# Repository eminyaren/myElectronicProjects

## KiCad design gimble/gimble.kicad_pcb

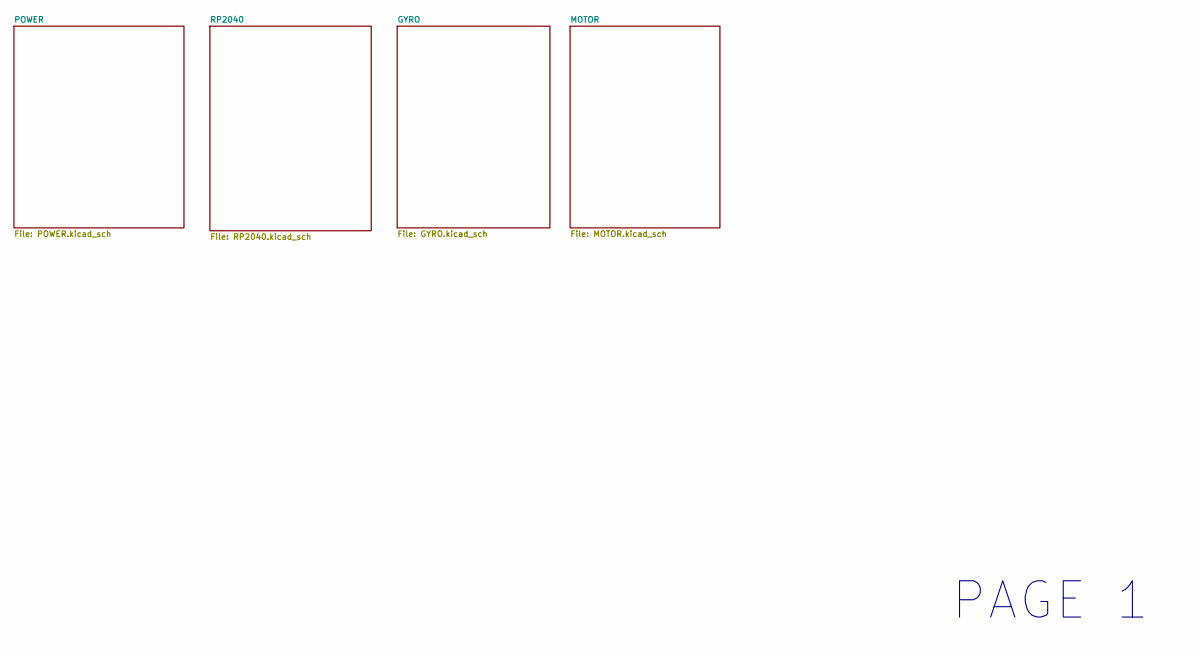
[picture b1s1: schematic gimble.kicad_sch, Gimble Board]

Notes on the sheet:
PAGE 1

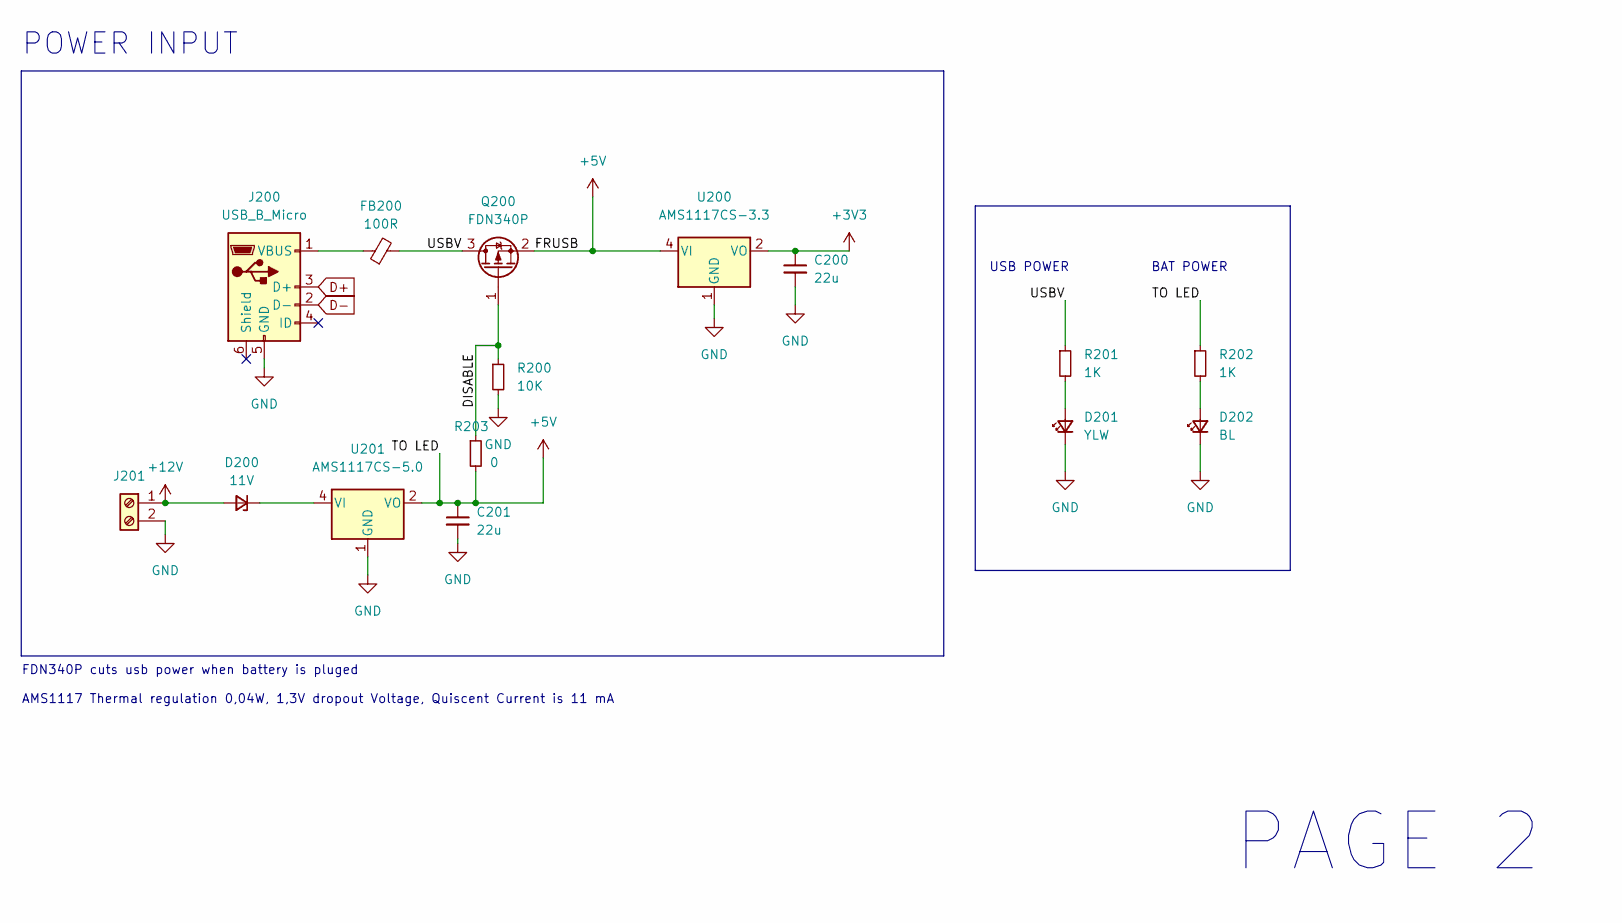
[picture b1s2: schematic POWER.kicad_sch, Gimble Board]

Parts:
C200, C201: 22u; CP_EIA-1608-08_AVX-J
D200: 11V; D_0603_1608Metric
D201: YLW; LED_0402_1005Metric
D202: BL; LED_0402_1005Metric
FB200: 100R; D_0603_1608Metric
J200: USB_B_Micro; USB_Micro-B_Molex_47346-0001
J201: Screw_Terminal_01x02; Molex_KK-254_AE-6410-02A_1x02_P2.54mm_Vertical
Q200: FDN340P; SOT-23
R200: 10K; R_0402_1005Metric
R201, R202: 1K; R_0402_1005Metric
R203: 0; R_0402_1005Metric
U200: AMS1117CS-3.3; SOIC-8_3.9x4.9mm_P1.27mm
U201: AMS1117CS-5.0; SOIC-8_3.9x4.9mm_P1.27mm

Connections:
+3V3: C200.1, U200.2 (VO), U200.3 (VO), U200.6 (VO), U200.7 (VO); also elsewhere on the board
+5V: C201.1, Q200.2 (S), R202.1, R203.2, U200.4 (VI), U201.2 (VO), U201.3 (VO), U201.6 (VO), U201.7 (VO); also elsewhere on the board
+12V: D200.2 (A), J201.1
/POWER/DISABLE: Q200.1 (G), R200.1, R203.1
/POWER/USBV: FB200.2, Q200.3 (D), R201.1
D+: J200.3 (D+); also elsewhere on the board
D-: J200.2 (D-); also elsewhere on the board
GND: C200.2, C201.2, D201.1 (K), D202.1 (K), J200.5 (GND), J201.2, R200.2, U200.1 (GND), U201.1 (GND); also elsewhere on the board
unnamed: D200.1 (K), U201.4 (VI)
unnamed: FB200.1, J200.1 (VBUS)
unnamed: D201.2 (A), R201.2
unnamed: D202.2 (A), R202.2

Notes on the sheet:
BAT POWER
PAGE 2
FDN340P cuts usb power when battery is pluged AMS1117 Thermal regulation 0,04W, 1,3V dropout Voltage, Quiscent Current is 11 mA
USB POWER
POWER INPUT

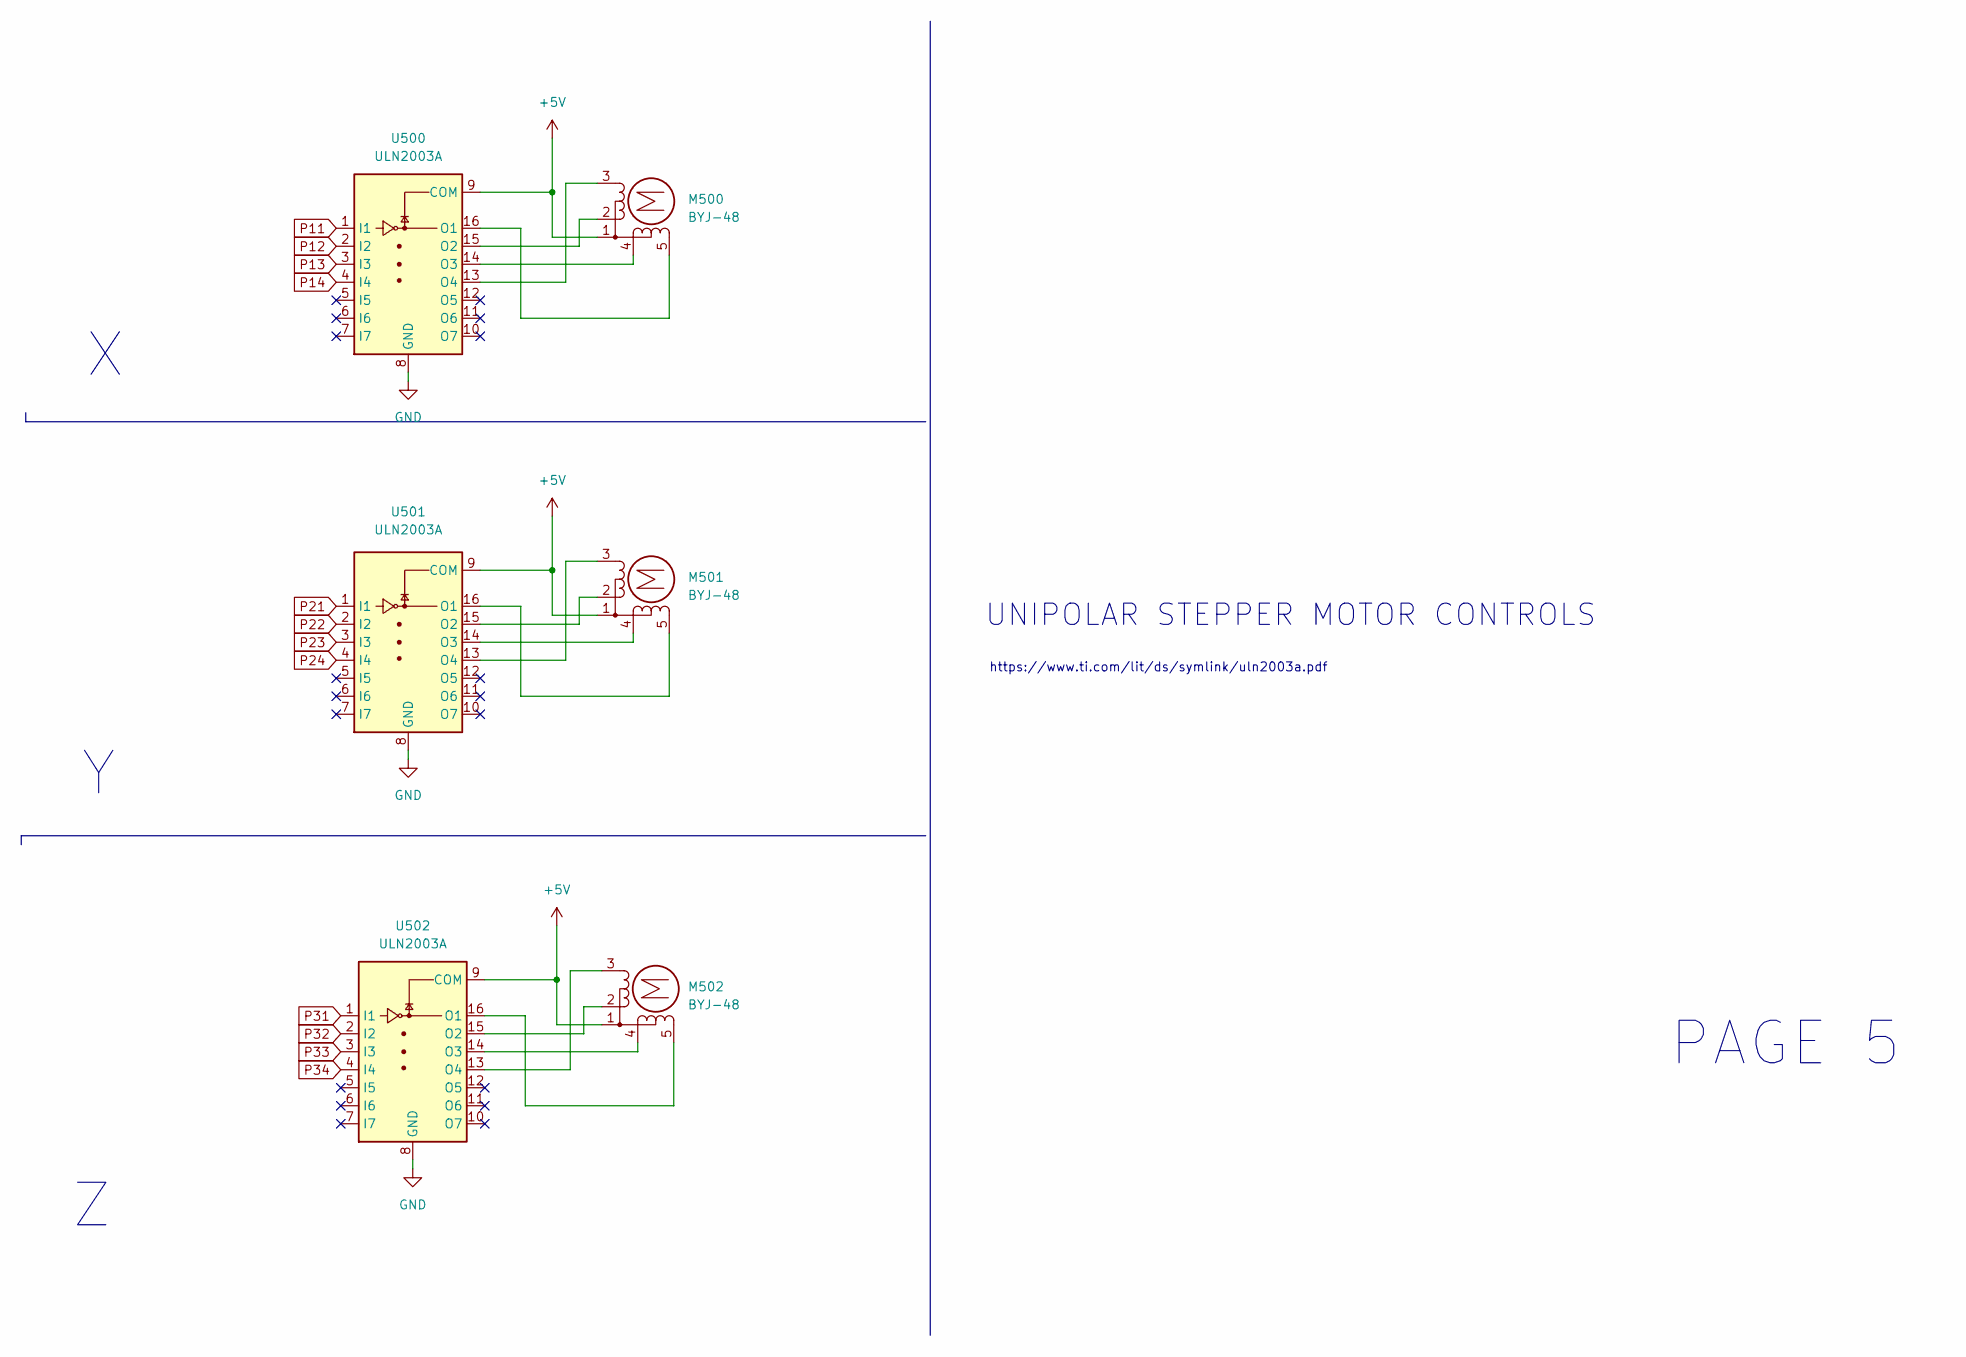
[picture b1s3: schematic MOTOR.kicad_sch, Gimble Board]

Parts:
M500, M501, M502: BYJ-48; PinHeader_1x05_P1.00mm_Vertical
U500, U501, U502: ULN2003A; SOIC-16_3.9x9.9mm_P1.27mm

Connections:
+5V: M500.1, M501.1, M502.1, U500.9 (COM), U501.9 (COM), U502.9 (COM); also elsewhere on the board
GND: U500.8 (GND), U501.8 (GND), U502.8 (GND); also elsewhere on the board
unnamed: M500.2, U500.15 (O2)
unnamed: M500.3 (-), U500.13 (O4)
unnamed: M500.4, U500.14 (O3)
unnamed: M500.5, U500.16 (O1)
unnamed: M501.3 (-), U501.13 (O4)
unnamed: M501.4, U501.14 (O3)
unnamed: M501.2, U501.15 (O2)
unnamed: M501.5, U501.16 (O1)
unnamed: M502.3 (-), U502.13 (O4)
unnamed: M502.4, U502.14 (O3)
unnamed: M502.2, U502.15 (O2)
unnamed: M502.5, U502.16 (O1)
P11: U500.1 (I1); also elsewhere on the board
P12: U500.2 (I2); also elsewhere on the board
P13: U500.3 (I3); also elsewhere on the board
P14: U500.4 (I4); also elsewhere on the board
P21: U501.1 (I1); also elsewhere on the board
P22: U501.2 (I2); also elsewhere on the board
P23: U501.3 (I3); also elsewhere on the board
P24: U501.4 (I4); also elsewhere on the board
P31: U502.1 (I1); also elsewhere on the board
P32: U502.2 (I2); also elsewhere on the board
P33: U502.3 (I3); also elsewhere on the board
P34: U502.4 (I4); also elsewhere on the board

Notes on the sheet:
UNIPOLAR STEPPER MOTOR CONTROLS
https://www.ti.com/lit/ds/symlink/uln2003a.pdf
PAGE 5

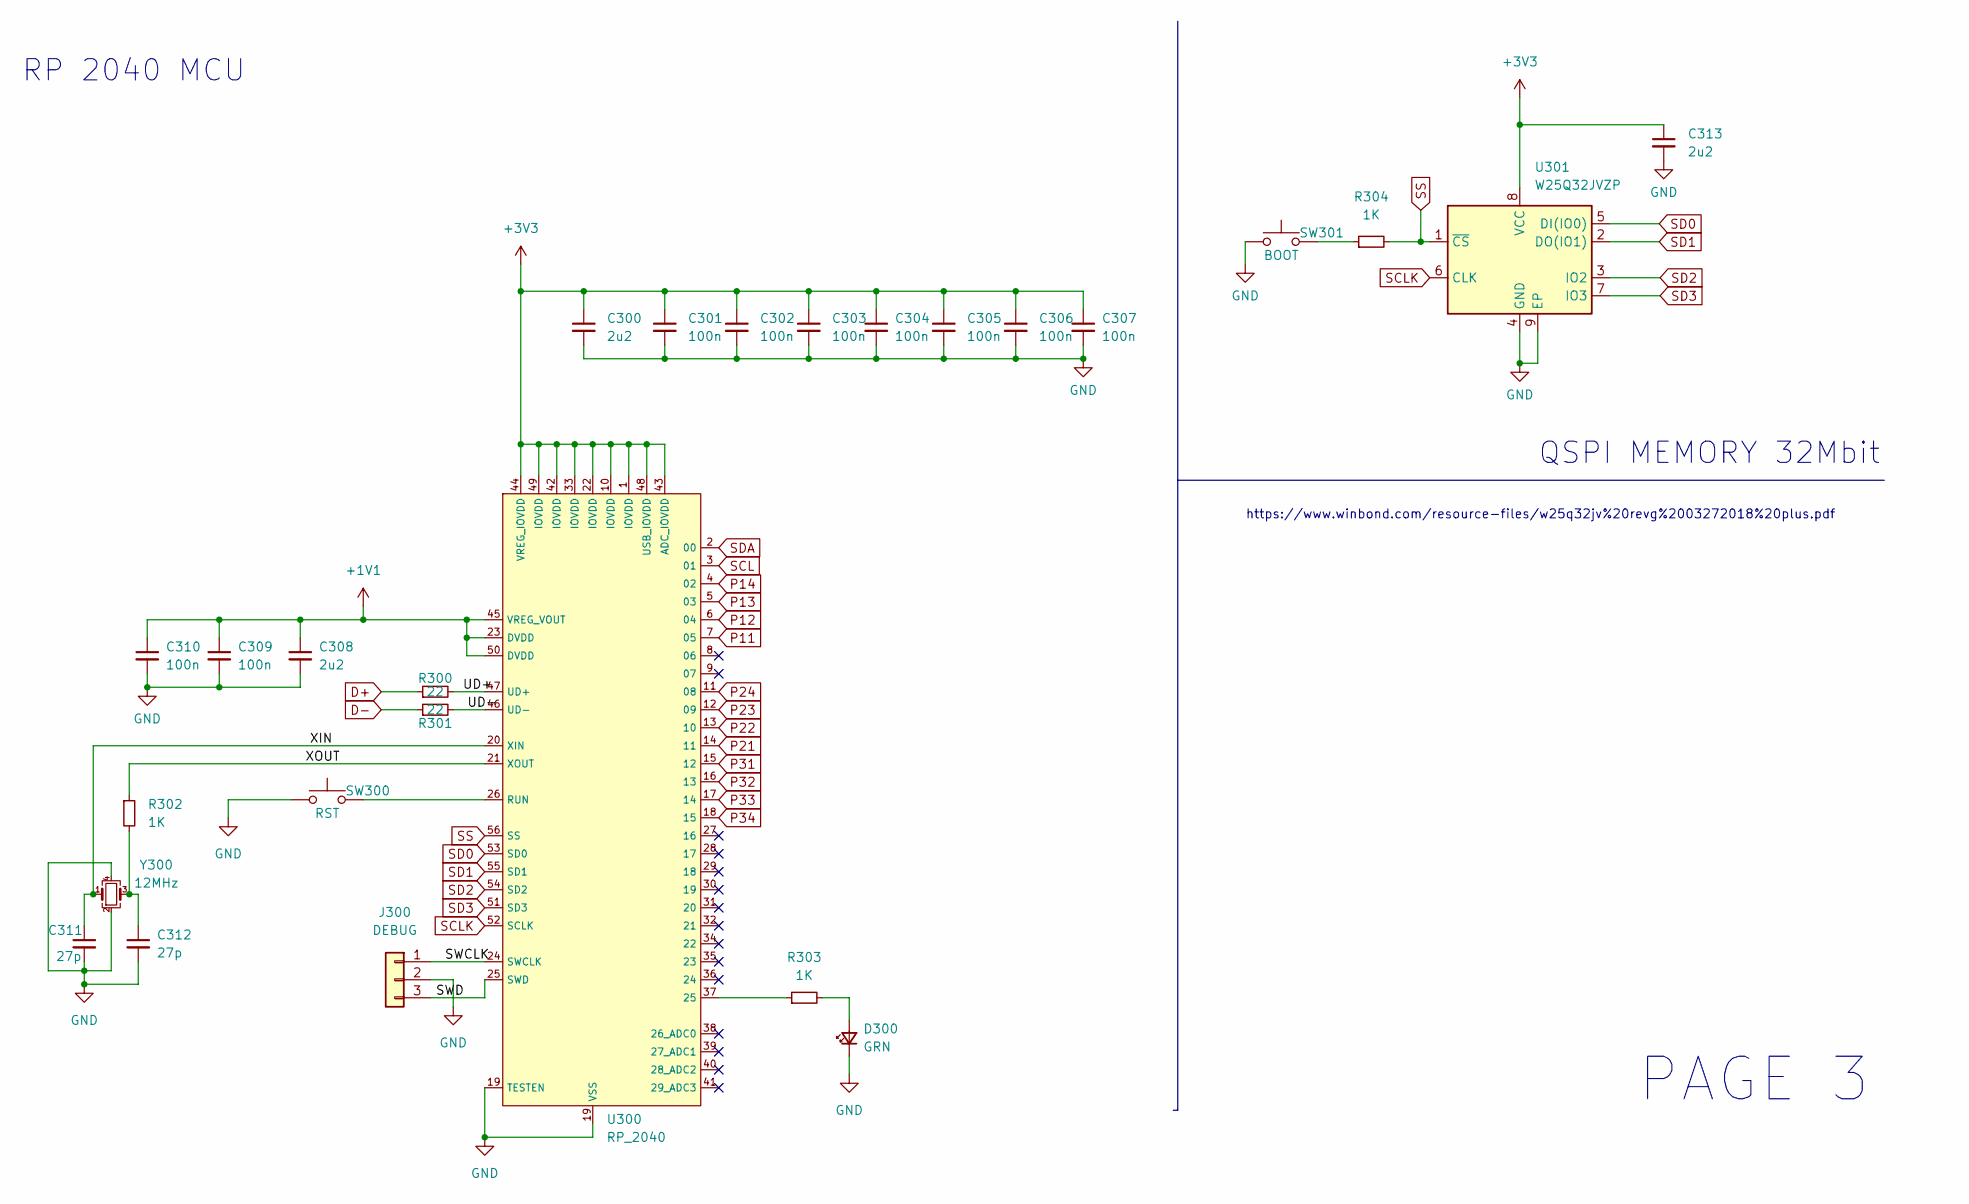
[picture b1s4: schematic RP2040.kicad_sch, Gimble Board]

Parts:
C300, C308, C313: 2u2; C_0603_1608Metric
C301, C302, C303, C304, C305, C306, C307, C309, C310: 100n; C_0402_1005Metric
C311, C312: 27p; C_0402_1005Metric
D300: GRN; LED_0402_1005Metric
J300: DEBUG; PinHeader_1x03_P2.54mm_Vertical
R300, R301: 22; R_0402_1005Metric
R302, R303, R304: 1K; R_0402_1005Metric
SW300: RST; SW_SPST_B3U-3000P
SW301: BOOT; SW_SPST_B3U-3000P
U300: RP_2040
U301: W25Q32JVZP; WSON-8-1EP_6x5mm_P1.27mm_EP3.4x4.3mm
Y300: 12MHz; Crystal_SMD_3225-4Pin_3.2x2.5mm

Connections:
+1V1: C308.1, C309.1, C310.1, U300.23 (DVDD), U300.45 (VREG_VOUT), U300.50 (DVDD)
+3V3: C300.1, C301.1, C302.1, C303.1, C304.1, C305.1, C306.1, C307.1, C313.1, U300.1 (IOVDD), U300.10 (IOVDD), U300.22 (IOVDD), U300.33 (IOVDD), U300.42 (IOVDD), U300.43 (ADC_IOVDD), U300.44 (VREG_IOVDD), U300.48 (USB_IOVDD), U300.49 (IOVDD), U301.8 (VCC); also elsewhere on the board
/RP2040/SWCLK: J300.1, U300.24 (SWCLK)
/RP2040/SWD: J300.3, U300.25 (SWD)
/RP2040/UD+: R300.2, U300.47 (UD+)
/RP2040/UD-: R301.2, U300.46 (UD-)
/RP2040/XIN: C311.1, U300.20 (XIN), Y300.1
/RP2040/XOUT: R302.1, U300.21 (XOUT)
D+: R300.1; also elsewhere on the board
D-: R301.1; also elsewhere on the board
GND: C300.2, C301.2, C302.2, C303.2, C304.2, C305.2, C306.2, C307.2, C308.2, C309.2, C310.2, C311.2, C312.2, C313.2, D300.1 (K), J300.2, SW300.1, SW301.1, U300.19 (TESTEN), U300.57, U301.4 (GND), U301.9 (EP), Y300.2, Y300.4; also elsewhere on the board
unnamed: C312.1, R302.2, Y300.3
unnamed: D300.2 (A), R303.2
unnamed: R304.1, SW301.2
unnamed: SW300.2, U300.26 (RUN)
unnamed: R303.1, U300.37 (25)
P11: U300.7 (05); also elsewhere on the board
P12: U300.6 (04); also elsewhere on the board
P13: U300.5 (03); also elsewhere on the board
P14: U300.4 (02); also elsewhere on the board
P21: U300.14 (11); also elsewhere on the board
P22: U300.13 (10); also elsewhere on the board
P23: U300.12 (09); also elsewhere on the board
P24: U300.11 (08); also elsewhere on the board
P31: U300.15 (12); also elsewhere on the board
P32: U300.16 (13); also elsewhere on the board
P33: U300.17 (14); also elsewhere on the board
P34: U300.18 (15); also elsewhere on the board
SCL: U300.3 (01); also elsewhere on the board
SCLK: U300.52 (SCLK), U301.6 (CLK)
SD0: U300.53 (SD0), U301.5 (DI(IO0))
SD1: U300.55 (SD1), U301.2 (DO(IO1))
SD2: U300.54 (SD2), U301.3 (IO2)
SD3: U300.51 (SD3), U301.7 (IO3)
SDA: U300.2 (00); also elsewhere on the board
SS: R304.2, U300.56 (SS), U301.1 (~CS)

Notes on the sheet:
QSPI MEMORY 32Mbit
PAGE 3
RP 2040 MCU
https://www.winbond.com/resource-files/w25q32jv%20revg%2003272018%20plus.pdf

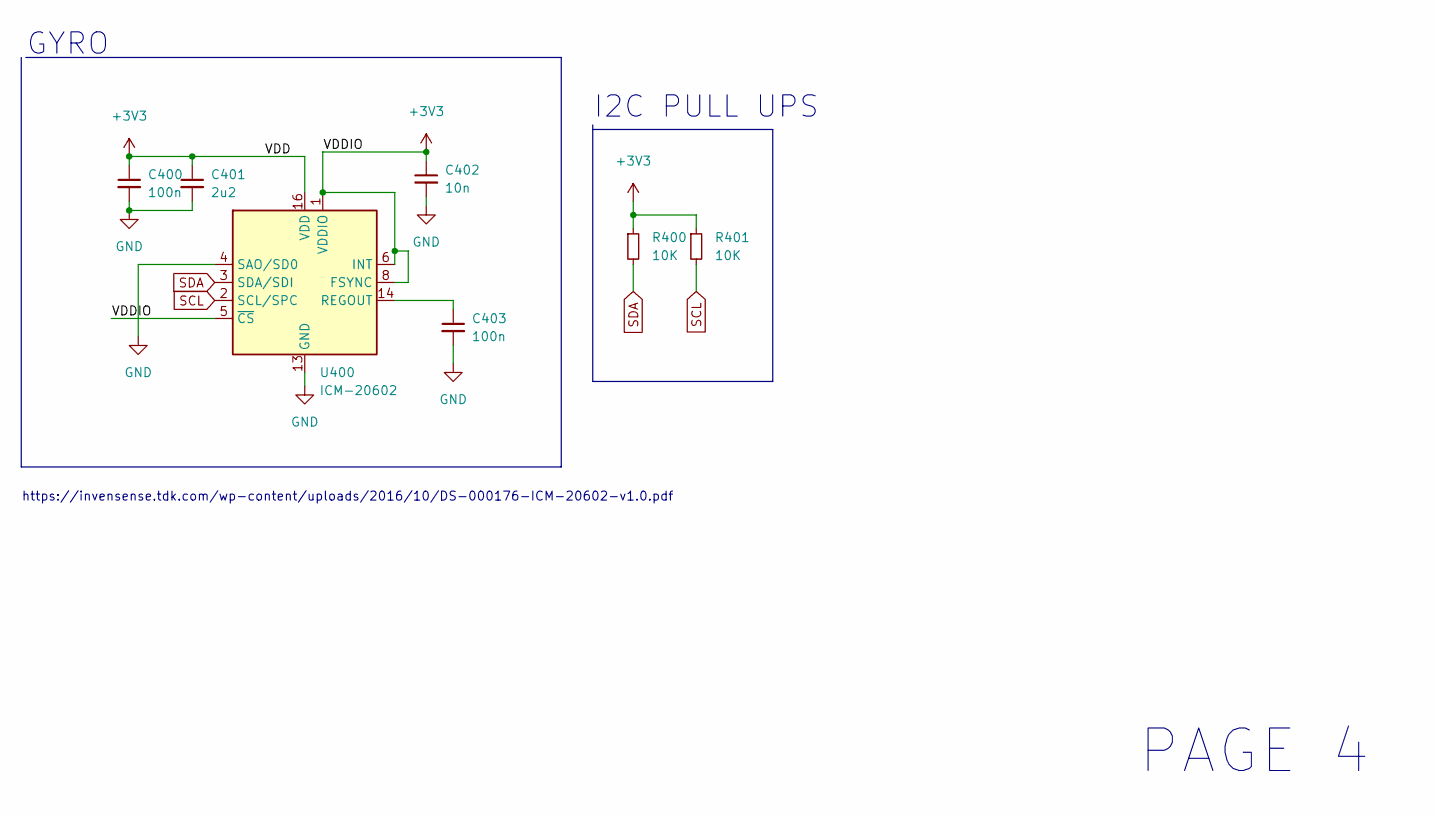
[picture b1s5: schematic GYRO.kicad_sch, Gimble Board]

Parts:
C400, C403: 100n; C_0402_1005Metric
C401: 2u2; C_0603_1608Metric
C402: 10n; C_0402_1005Metric
R400, R401: 10K; R_0402_1005Metric
U400: ICM-20602; LGA-16_3x3mm_P0.5mm_LayoutBorder3x5y

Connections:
+3V3: C400.1, C401.1, C402.1, R400.1, R401.1, U400.1 (VDDIO), U400.5 (~CS), U400.6 (INT), U400.8 (FSYNC), U400.16 (VDD); also elsewhere on the board
GND: C400.2, C401.2, C402.2, C403.2, U400.4 (SAO/SD0), U400.9 (GND), U400.10 (GND), U400.11 (GND), U400.12 (GND), U400.13 (GND), U400.15 (GND); also elsewhere on the board
unnamed: C403.1, U400.14 (REGOUT)
SCL: R401.2, U400.2 (SCL/SPC); also elsewhere on the board
SDA: R400.2, U400.3 (SDA/SDI); also elsewhere on the board

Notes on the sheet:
I2C PULL UPS
https://invensense.tdk.com/wp-content/uploads/2016/10/DS-000176-ICM-20602-v1.0.pdf
PAGE 4
GYRO

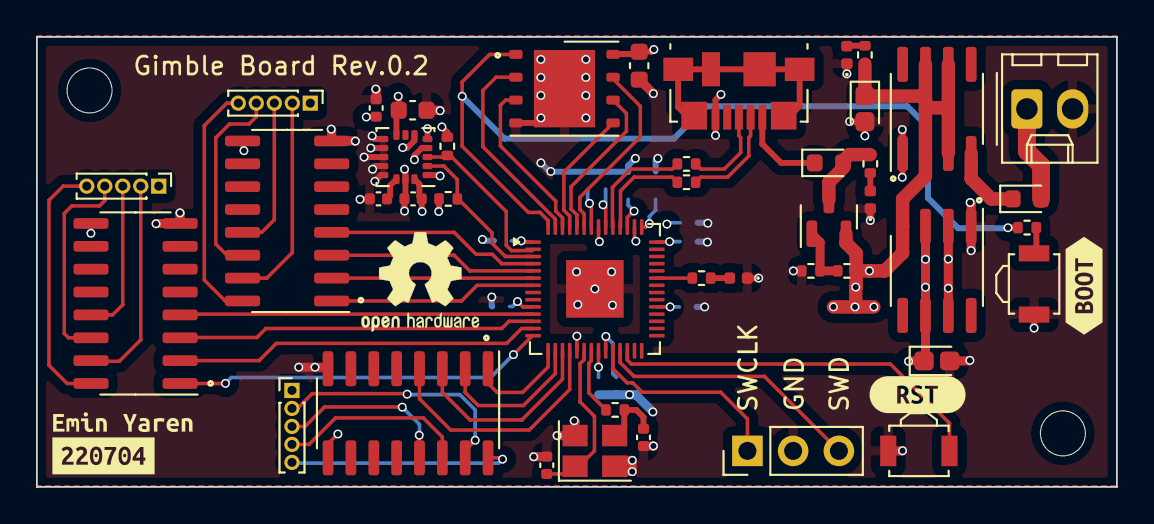
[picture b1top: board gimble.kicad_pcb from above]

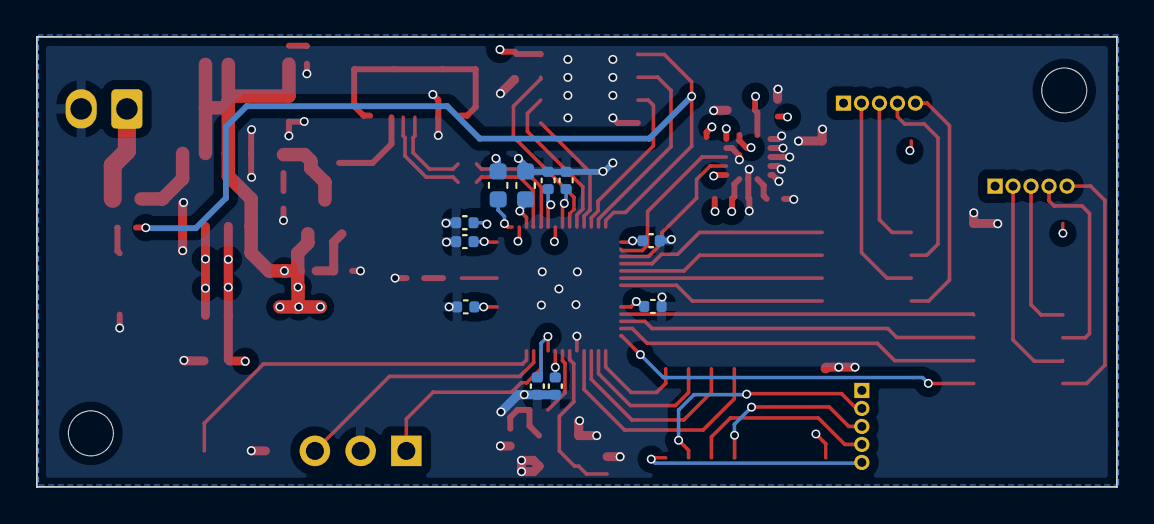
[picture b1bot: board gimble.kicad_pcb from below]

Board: 4 copper layers, 60.0 x 25.0 mm, 58 parts (11 on the bottom side), 57 nets.

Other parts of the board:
kibuzzard-62C2D4AD: G***; kibuzzard-62C2D4AD
kibuzzard-62C2D491: G***; kibuzzard-62C2D491
kibuzzard-62C2DB9E: G***; kibuzzard-62C2DB9E
kibuzzard-62C2DC45: G***; kibuzzard-62C2DC45

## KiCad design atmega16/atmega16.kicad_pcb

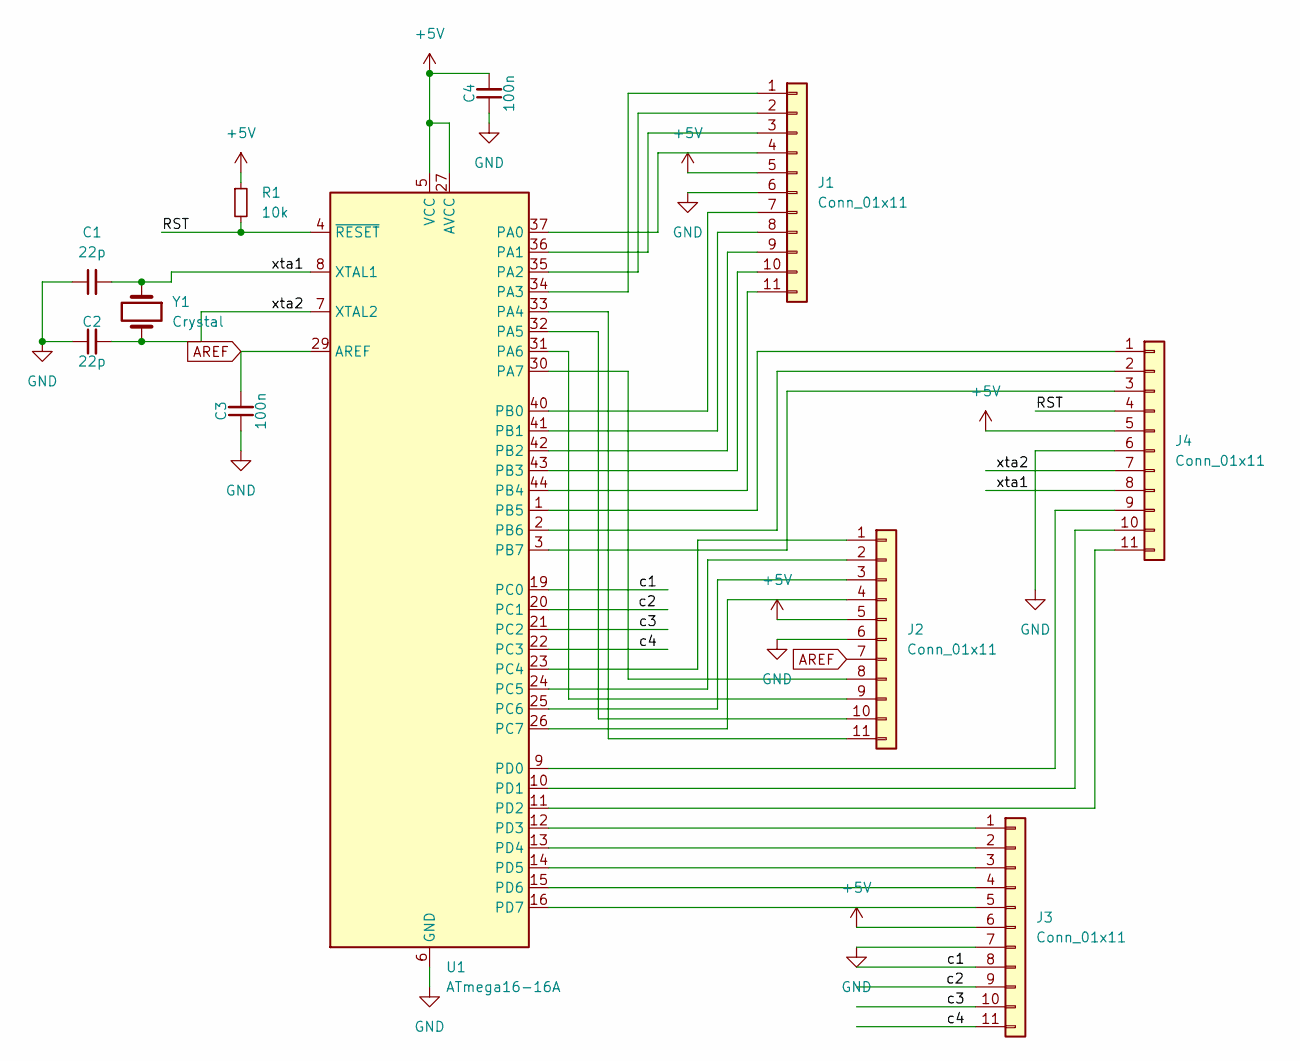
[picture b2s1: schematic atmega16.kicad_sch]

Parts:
C1, C2: 22p; C_Disc_D3.0mm_W2.0mm_P2.50mm
C3, C4: 100n; C_Disc_D3.0mm_W2.0mm_P2.50mm
J1, J2, J3, J4: Conn_01x11; PinHeader_1x11_P2.54mm_Vertical
R1: 10k; R_Axial_DIN0204_L3.6mm_D1.6mm_P7.62mm_Horizontal
U1: ATmega16-16A; TQFP-44_10x10mm_P0.8mm
Y1: Crystal; Crystal_HC49-4H_Vertical

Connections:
+5V: C4.2, J1.5, J2.5, J3.6, J4.5, R1.1, U1.5 (VCC), U1.17 (VCC), U1.27 (AVCC), U1.38 (VCC)
/RST: J4.4, R1.2, U1.4 (~RESET)
/c1: J3.8, U1.19 (PC0)
/c2: J3.9, U1.20 (PC1)
/c3: J3.10, U1.21 (PC2)
/c4: J3.11, U1.22 (PC3)
/xta1: C1.2, J4.8, U1.8 (XTAL1), Y1.1
/xta2: C2.2, J4.7, U1.7 (XTAL2), Y1.2
AREF: C3.2, J2.7, U1.29 (AREF)
GND: C1.1, C2.1, C3.1, C4.1, J1.6, J2.6, J3.7, J4.6, U1.6 (GND), U1.18 (GND), U1.28 (GND), U1.39 (GND)
unnamed: J4.1, U1.1 (PB5)
unnamed: J4.2, U1.2 (PB6)
unnamed: J4.3, U1.3 (PB7)
unnamed: J4.9, U1.9 (PD0)
unnamed: J4.10, U1.10 (PD1)
unnamed: J4.11, U1.11 (PD2)
unnamed: J3.1, U1.12 (PD3)
unnamed: J3.2, U1.13 (PD4)
unnamed: J3.3, U1.14 (PD5)
unnamed: J3.4, U1.15 (PD6)
unnamed: J3.5, U1.16 (PD7)
unnamed: J2.1, U1.23 (PC4)
unnamed: J2.2, U1.24 (PC5)
unnamed: J2.3, U1.25 (PC6)
unnamed: J2.4, U1.26 (PC7)
unnamed: J2.8, U1.30 (PA7)
unnamed: J2.9, U1.31 (PA6)
unnamed: J2.10, U1.32 (PA5)
unnamed: J2.11, U1.33 (PA4)
unnamed: J1.1, U1.34 (PA3)
unnamed: J1.2, U1.35 (PA2)
unnamed: J1.3, U1.36 (PA1)
unnamed: J1.4, U1.37 (PA0)
unnamed: J1.7, U1.40 (PB0)
unnamed: J1.8, U1.41 (PB1)
unnamed: J1.9, U1.42 (PB2)
unnamed: J1.10, U1.43 (PB3)
unnamed: J1.11, U1.44 (PB4)

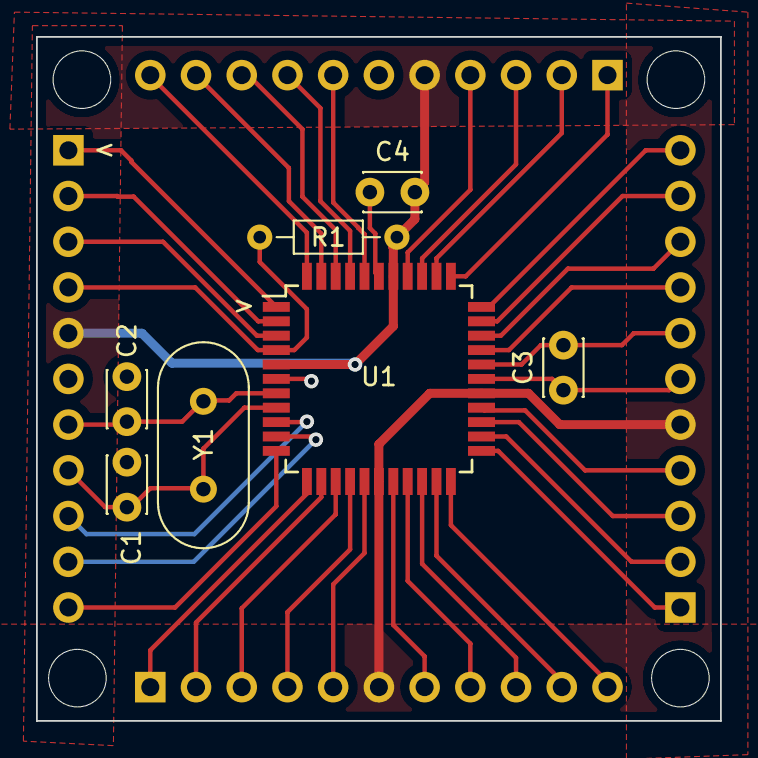
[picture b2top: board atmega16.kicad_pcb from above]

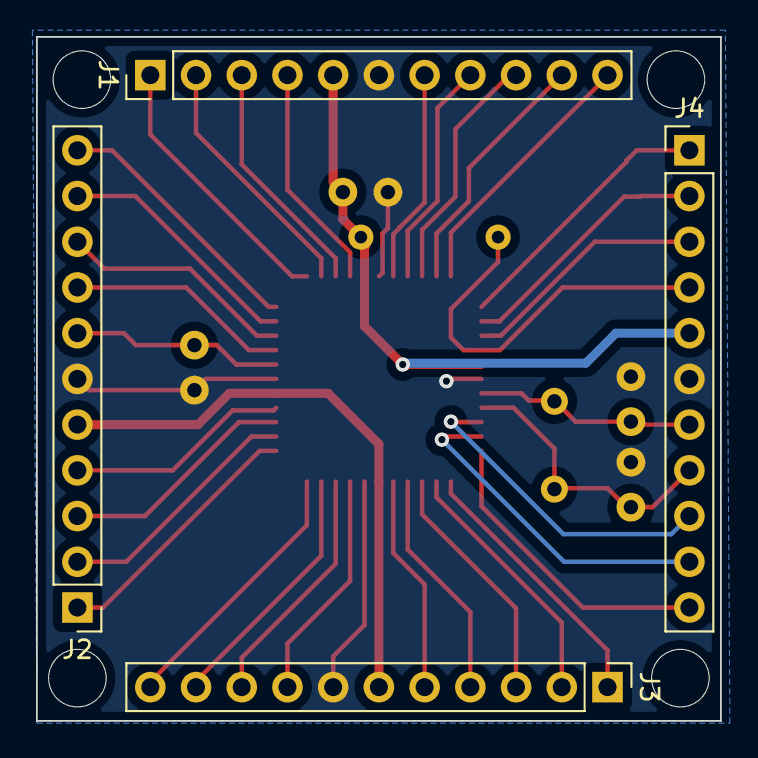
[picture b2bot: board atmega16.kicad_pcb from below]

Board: 2 copper layers, 38.0 x 38.0 mm, 11 parts (4 on the bottom side), 38 nets.

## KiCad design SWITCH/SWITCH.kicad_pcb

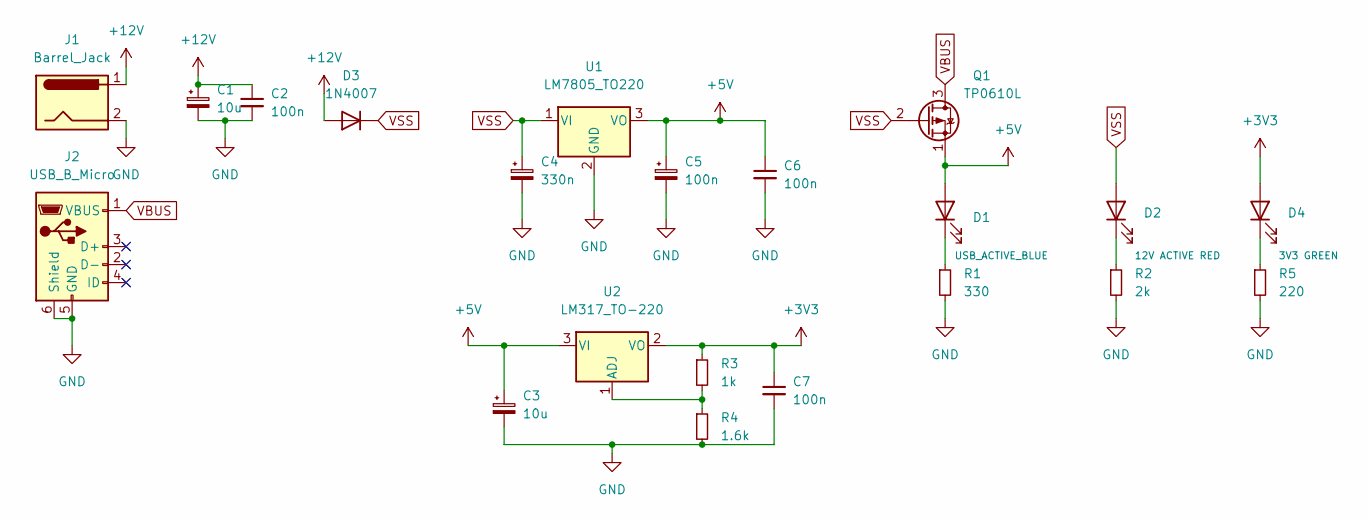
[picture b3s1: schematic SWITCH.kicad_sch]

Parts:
C1, C3: 10u; CP_Radial_D5.0mm_P2.50mm
C2, C6, C7: 100n; C_Disc_D3.4mm_W2.1mm_P2.50mm
C4: 330n; CP_Radial_Tantal_D4.5mm_P5.00mm
C5: 100n; CP_Radial_Tantal_D4.5mm_P5.00mm
D1: USB_ACTIVE_BLUE; LED_D3.0mm
D2: 12V ACTIVE RED; LED_D3.0mm
D3: 1N4007; D_DO-41_SOD81_P10.16mm_Horizontal
D4: 3V3 GREEN; LED_D3.0mm
J1: Barrel_Jack; BarrelJack_Horizontal
J2: USB_B_Micro; USB_Micro-B_Amphenol_10103594-0001LF_Horizontal
Q1: TP0610L; TO-92L_Inline
R1: 330; R_Axial_DIN0204_L3.6mm_D1.6mm_P7.62mm_Horizontal
R2: 2k; R_Axial_DIN0204_L3.6mm_D1.6mm_P7.62mm_Horizontal
R3: 1k; R_Axial_DIN0204_L3.6mm_D1.6mm_P7.62mm_Horizontal
R4: 1.6k; R_Axial_DIN0204_L3.6mm_D1.6mm_P7.62mm_Horizontal
R5: 220; R_Axial_DIN0204_L3.6mm_D1.6mm_P7.62mm_Horizontal
U1: LM7805_TO220; TO-220-3_Vertical
U2: LM317_TO-220; TO-220-3_Vertical

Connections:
+3V3: C7.1, D4.2 (A), R3.1, U2.2 (VO)
+5V: C3.1, C5.1, C6.1, D1.2 (A), Q1.1 (S), U1.3 (VO), U2.3 (VI)
+12V: C1.1, C2.1, D3.2 (A), J1.1
GND: C1.2, C2.2, C3.2, C4.2, C5.2, C6.2, C7.2, J1.2, J1.3, J2.5 (GND), J2.6 (Shield), R1.2, R2.2, R4.2, R5.2, U1.2 (GND)
unnamed: D1.1 (K), R1.1
unnamed: D2.1 (K), R2.1
unnamed: D4.1 (K), R5.1
unnamed: R3.2, R4.1, U2.1 (ADJ)
VBUS: J2.1 (VBUS), Q1.3 (D)
VSS: C4.1, D2.2 (A), D3.1 (K), Q1.2 (G), U1.1 (VI)

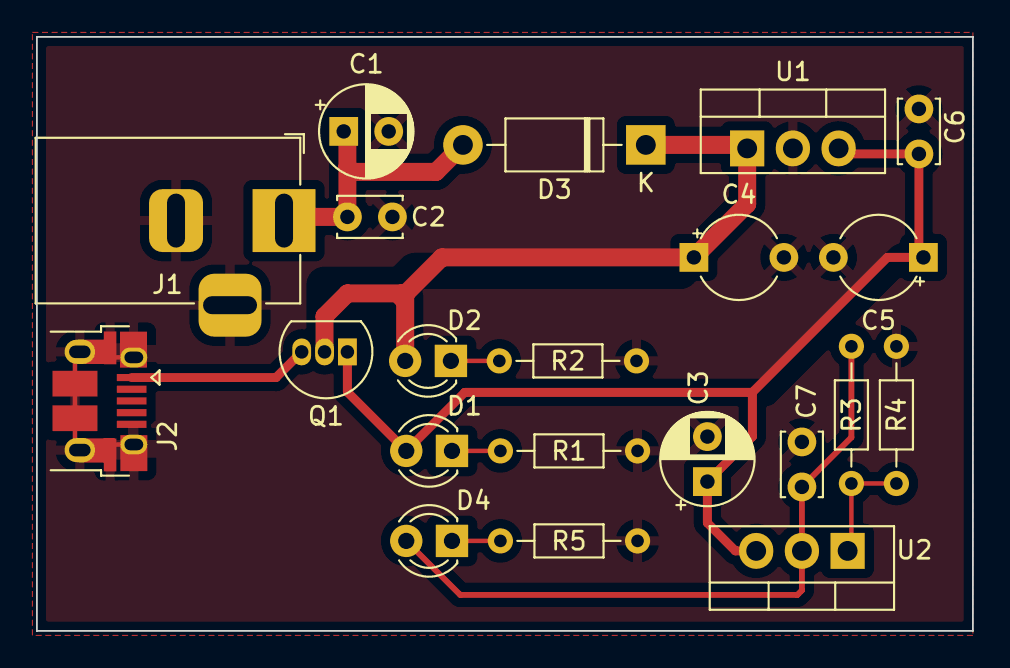
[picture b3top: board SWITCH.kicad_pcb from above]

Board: 2 copper layers, 52.0 x 33.0 mm, 21 parts (0 on the bottom side), 10 nets.
